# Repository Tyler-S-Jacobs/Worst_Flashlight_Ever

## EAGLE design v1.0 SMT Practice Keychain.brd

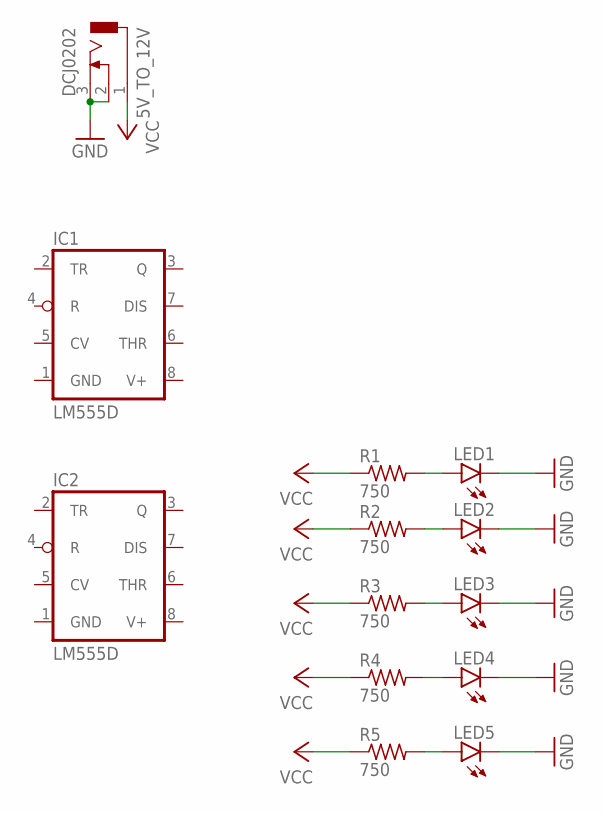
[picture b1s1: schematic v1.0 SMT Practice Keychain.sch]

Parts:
5V_TO_12V: DCJ0202
IC1, IC2: LM555D; SO08
LED1, LED2, LED3, LED4, LED5: LEDCHIPLED_1206; CHIPLED_1206
R1, R2, R3, R4, R5: 750; R1206

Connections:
GND: 5V_TO_12V.2, 5V_TO_12V.3, IC1.1 (GND), IC2.1 (GND), LED1.C, LED2.C, LED3.C, LED4.C, LED5.C
unnamed: LED1.A, R1.2
unnamed: LED2.A, R2.2
unnamed: LED3.A, R3.2
unnamed: LED4.A, R4.2
unnamed: LED5.A, R5.2
V+: IC1.8 (V+), IC2.8 (V+)
VCC: 5V_TO_12V.1, R1.1, R2.1, R3.1, R4.1, R5.1

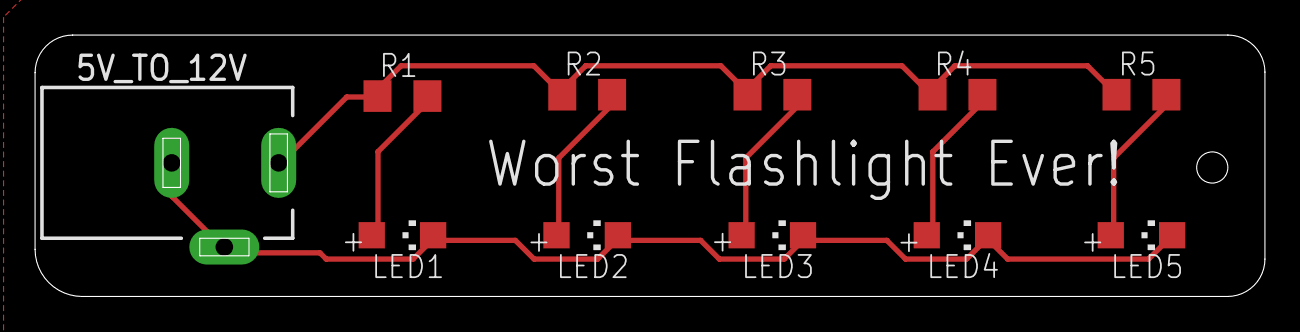
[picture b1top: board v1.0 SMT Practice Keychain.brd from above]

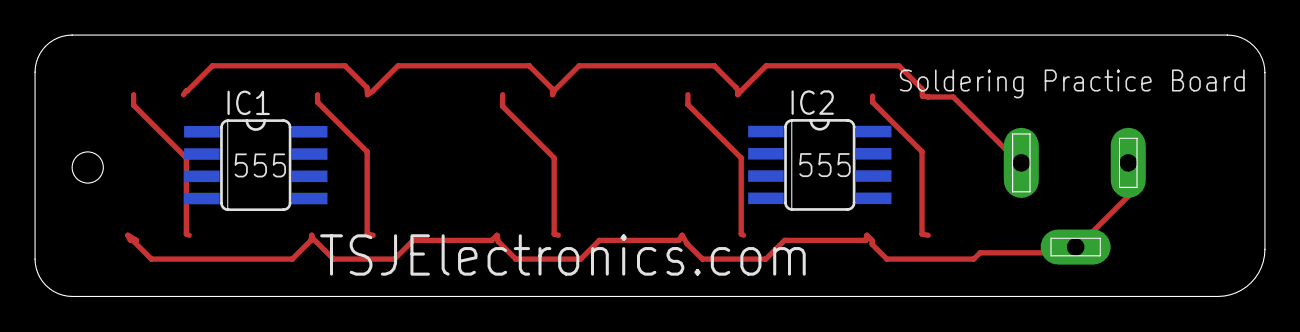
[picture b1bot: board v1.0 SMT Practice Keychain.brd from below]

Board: 2 copper layers, 70.1 x 14.9 mm, 13 parts (2 on the bottom side), 8 nets.
